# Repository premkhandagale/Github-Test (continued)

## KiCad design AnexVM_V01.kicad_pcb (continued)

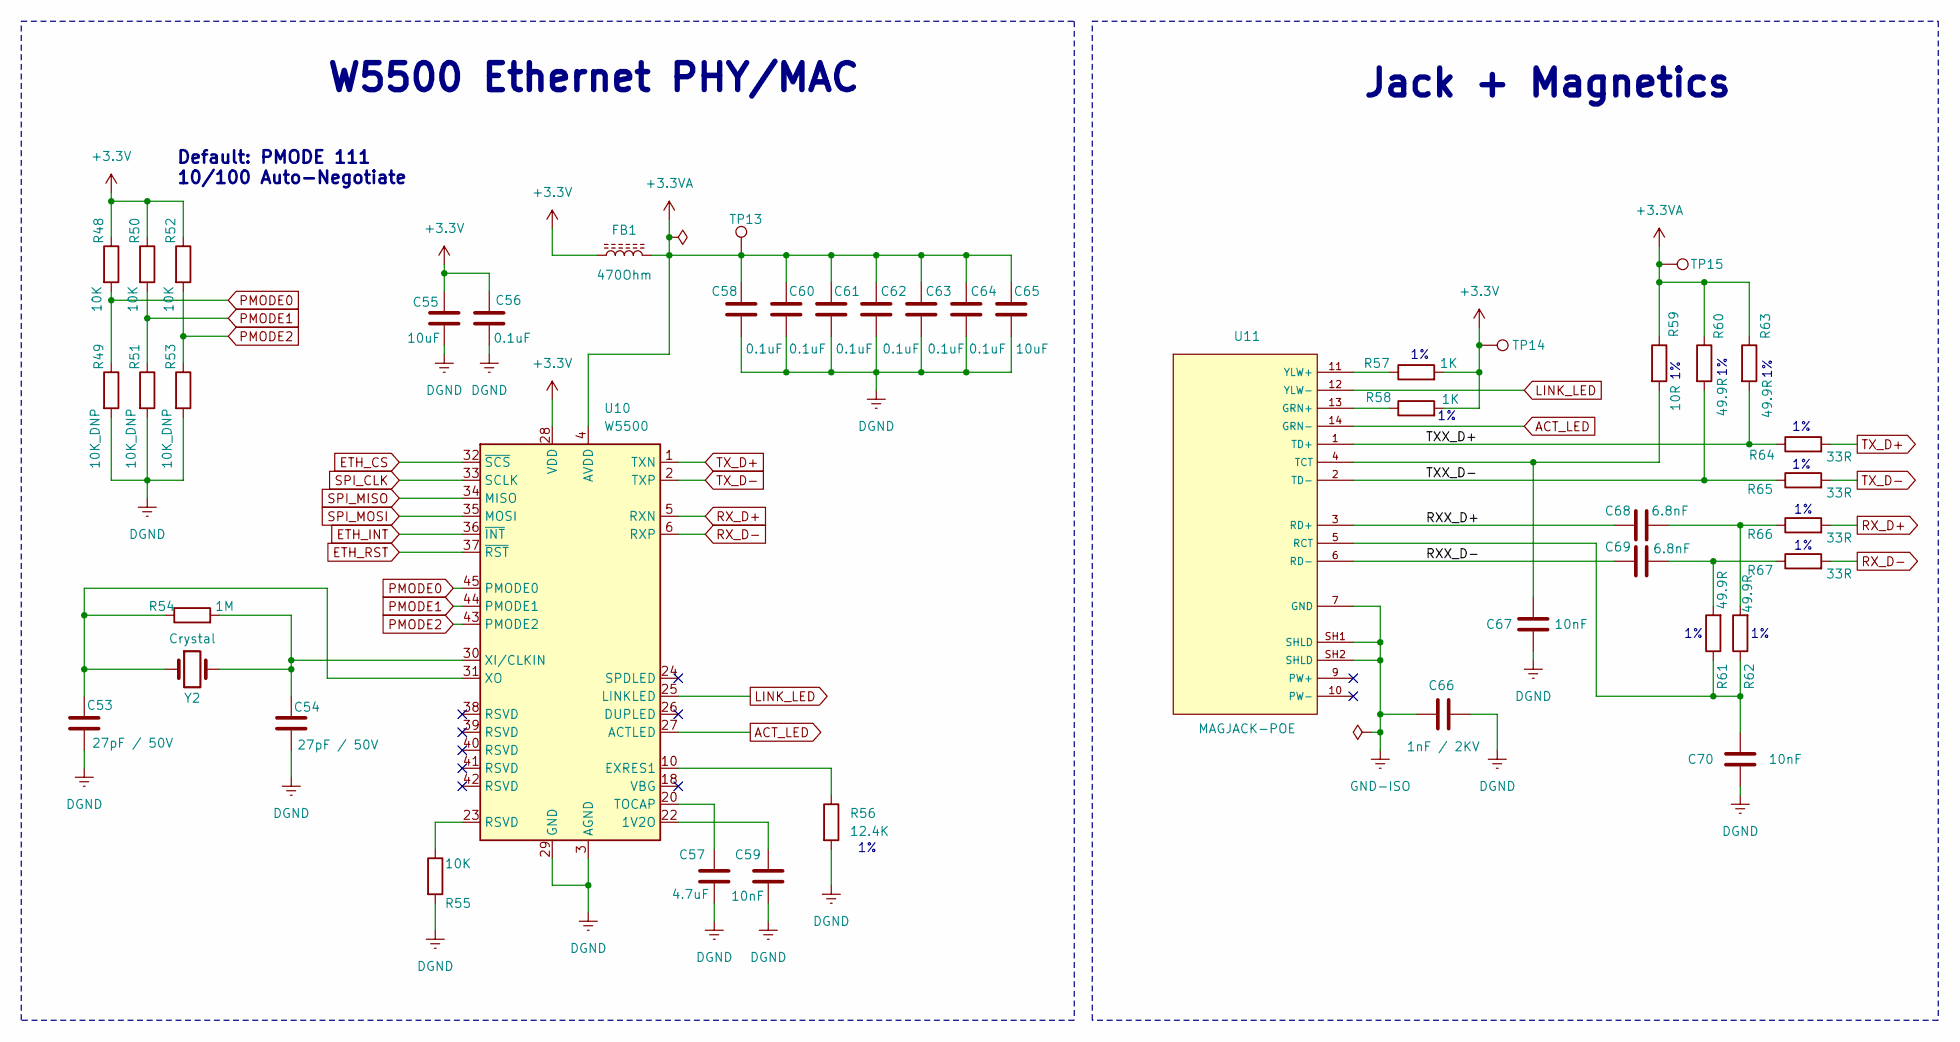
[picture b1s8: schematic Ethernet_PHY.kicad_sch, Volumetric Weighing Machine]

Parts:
C53, C54: 27pF / 50V; C_0603_1608Metric
C55, C65: 10uF; C_0805_2012Metric
C56, C58, C60, C61, C62, C63, C64: 0.1uF; C_0603_1608Metric
C57: 4.7uF; C_0603_1608Metric
C59, C67, C70: 10nF; C_0603_1608Metric
C66: 1nF / 2KV; C_1812_4532Metric
C68, C69: 6.8nF; C_0603_1608Metric
FB1: 470Ohm; D_0603_1608Metric
R48, R50, R52, R55: 10K; R_0603_1608Metric
R49, R51, R53: 10K_DNP; R_0603_1608Metric
R54: 1M; R_0603_1608Metric
R56: 12.4K; R_0603_1608Metric
R57, R58: 1K; R_0603_1608Metric
R59: 10R; R_0603_1608Metric
R60, R61, R62, R63: 49.9R; R_0603_1608Metric
R64, R65, R66, R67: 33R; R_0603_1608Metric
TP13, TP14, TP15: TestPoint; TestPoint_Pad_D1.0mm
U10: W5500; LQFP-48_7x7mm_P0.5mm
U11: MAGJACK-POE; LPJ0284GDNL
Y2: Crystal; XTAL_ECS-250-18-30-JGN-TR

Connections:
+3.3V: C55.1, C56.1, FB1.1, R48.1, R50.1, R52.1, R57.2, R58.2, TP14.1, U10.28 (VDD); also elsewhere on the board
+3.3VA: C58.1, C60.1, C61.1, C62.1, C63.1, C64.1, C65.1, FB1.2, R59.1, R60.1, R63.1, TP13.1, TP15.1, U10.4 (AVDD), U10.8 (AVDD), U10.11 (AVDD), U10.15 (AVDD), U10.17 (AVDD), U10.21 (AVDD)
/Ethernet_PHY/RXX_D+: C68.1, U11.3 (RD+)
/Ethernet_PHY/RXX_D-: C69.1, U11.6 (RD-)
/Ethernet_PHY/TXX_D+: R63.2, R64.1, U11.1 (TD+)
/Ethernet_PHY/TXX_D-: R60.2, R65.1, U11.2 (TD-)
ACT_LED: U10.27 (ACTLED), U11.14 (GRN-)
DGND: C53.2, C54.2, C55.2, C56.2, C57.2, C58.2, C59.2, C60.2, C61.2, C62.2, C63.2, C64.2, C65.2, C66.2, C67.1, C70.1, R49.2, R51.2, R53.2, R55.2, R56.2, U10.3 (AGND), U10.9 (AGND), U10.14 (AGND), U10.16 (AGND), U10.19 (AGND), U10.29 (GND), U10.48 (AGND); also elsewhere on the board
ETH_CS: U10.32 (~SCS); also elsewhere on the board
ETH_INT: U10.36 (~INT); also elsewhere on the board
ETH_RST: U10.37 (~RST); also elsewhere on the board
GND-ISO: C66.1, U11.7 (GND), U11.SH1 (SHLD), U11.SH2 (SHLD)
LINK_LED: U10.25 (LINKLED), U11.12 (YLW-)
unnamed: C68.2, R62.2, R66.1
unnamed: C69.2, R61.2, R67.1
unnamed: R55.1, U10.23 (RSVD)
unnamed: C59.1, U10.22 (1V2O)
unnamed: R56.1, U10.10 (EXRES1)
unnamed: C57.1, U10.20 (TOCAP)
unnamed: C54.1, R54.2, U10.30 (XI/CLKIN), Y2.2
unnamed: C53.1, R54.1, U10.31 (XO), Y2.1
unnamed: R58.1, U11.13 (GRN+)
unnamed: C70.2, R61.1, R62.1, U11.5 (RCT)
unnamed: C67.2, R59.2, U11.4 (TCT)
unnamed: R57.1, U11.11 (YLW+)
PMODE0: R48.2, R49.1, U10.45 (PMODE0)
PMODE1: R50.2, R51.1, U10.44 (PMODE1)
PMODE2: R52.2, R53.1, U10.43 (PMODE2)
RX_D+: R66.2, U10.5 (RXN)
RX_D-: R67.2, U10.6 (RXP)
SPI_CLK: U10.33 (SCLK); also elsewhere on the board
SPI_MISO: U10.34 (MISO); also elsewhere on the board
SPI_MOSI: U10.35 (MOSI); also elsewhere on the board
TX_D+: R64.2, U10.1 (TXN)
TX_D-: R65.2, U10.2 (TXP)

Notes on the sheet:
Jack + Magnetics
Default: PMODE 111 10/100 Auto-Negotiate
W5500 Ethernet PHY/MAC

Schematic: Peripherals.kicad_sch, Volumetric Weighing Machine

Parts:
C36, C40, C41, C42, C43, C44: 1uF; C_0603_1608Metric
C37, C38, C39, C45: 0.1uF; C_0603_1608Metric
J9: DB9-01S; DLS1XS5AK40X
J10, J12, J13: Conn_01x04_Pin; PinHeader_1x04_P2.54mm_Vertical
J11: JHD539; PinHeader_1x12_P2.54mm_Vertical
R41: 10K; R_0603_1608Metric
R42: 560R; R_0603_1608Metric
RV1: 10K_POT; Potentiometer_Bourns_3296W_Vertical
TP12: TestPoint; TestPoint_Pad_D1.0mm
U7: TXS0102DCUR; SOP50P310X90-8N
U8: MAX232; SOIC-16_3.9x9.9mm_P1.27mm

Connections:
+3.3V: C37.2, R41.1, U7.3 (VCCA); also elsewhere on the board
+5V: C38.2, C39.2, C40.2, C44.1, C45.1, J10.1, J11.2 (VDD), J12.1, J13.1, R42.2, RV1.3, TP12.1, U7.7 (VCCB), U8.16 (VCC); also elsewhere on the board
ATMEGA_RX_5V: U7.1 (B2); also elsewhere on the board
ATMEGA_TX_5V: U7.8 (B1); also elsewhere on the board
DGND: C37.1, C38.1, C39.1, C40.1, C41.1, C42.1, C44.2, C45.2, J9.5, J9.MH1, J9.MH2, J10.4, J11.1 (VSS), J11.16 (LED(-)), J12.4, J13.4, RV1.1, U7.2 (GND), U8.15 (GND); also elsewhere on the board
ESP32_RX_3V3: U7.4 (A2); also elsewhere on the board
ESP32_TX_3V3: U7.5 (A1); also elsewhere on the board
LCD_D4: J11.11 (D4); also elsewhere on the board
LCD_D5: J11.12 (D5); also elsewhere on the board
LCD_D6: J11.13 (D6); also elsewhere on the board
LCD_D7: J11.14 (D7); also elsewhere on the board
LCD_EN: J11.6 (E); also elsewhere on the board
LCD_RS: J11.4 (RS); also elsewhere on the board
LCD_RW: J11.5 (R/W); also elsewhere on the board
unnamed: J11.15 (LED(+)), R42.1
unnamed: J11.3 (VO), RV1.2
unnamed: R41.2, U7.6 (OE)
unnamed: C36.2, U8.1 (C1+)
unnamed: C36.1, U8.3 (C1-)
unnamed: C43.2, U8.4 (C2+)
unnamed: C43.1, U8.5 (C2-)
unnamed: J9.3, U8.13 (R1IN)
unnamed: J9.2, U8.14 (T1OUT)
unnamed: C41.2, U8.2 (VS+)
unnamed: C42.2, U8.6 (VS-)
RXD2: U8.12 (R1OUT); also elsewhere on the board
S1_ECHO: J10.3; also elsewhere on the board
S1_TRIG: J10.2; also elsewhere on the board
S2_ECHO: J12.3; also elsewhere on the board
S2_TRIG: J12.2; also elsewhere on the board
S3_ECHO: J13.3; also elsewhere on the board
S3_TRIG: J13.2; also elsewhere on the board
TXD2: U8.11 (T1IN); also elsewhere on the board

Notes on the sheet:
Logic Level Converter - Bi-Directional
16*4 LCD Display
Sensor_3
UART_TO_RS232_INTERFACE
Sensor_1
Sensor_2
Ultrasonic_Module

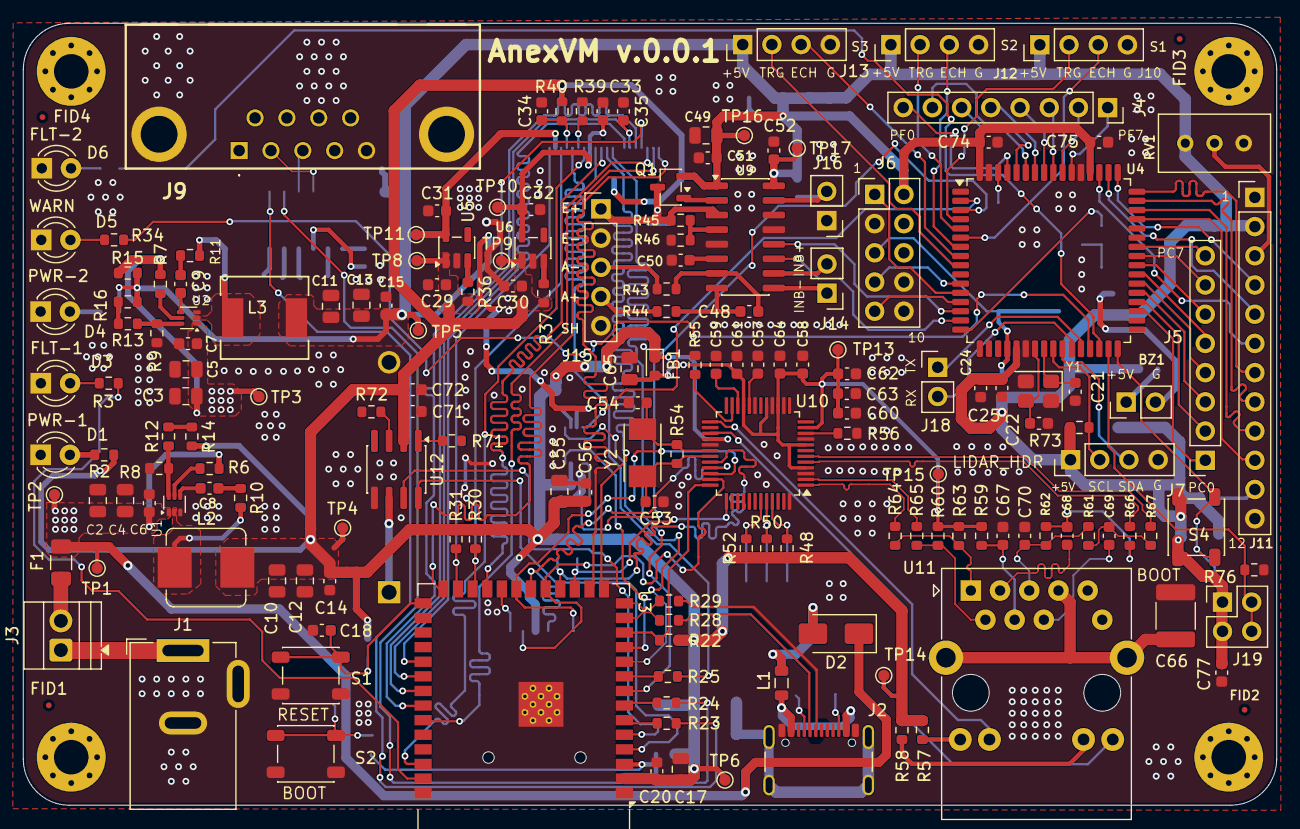
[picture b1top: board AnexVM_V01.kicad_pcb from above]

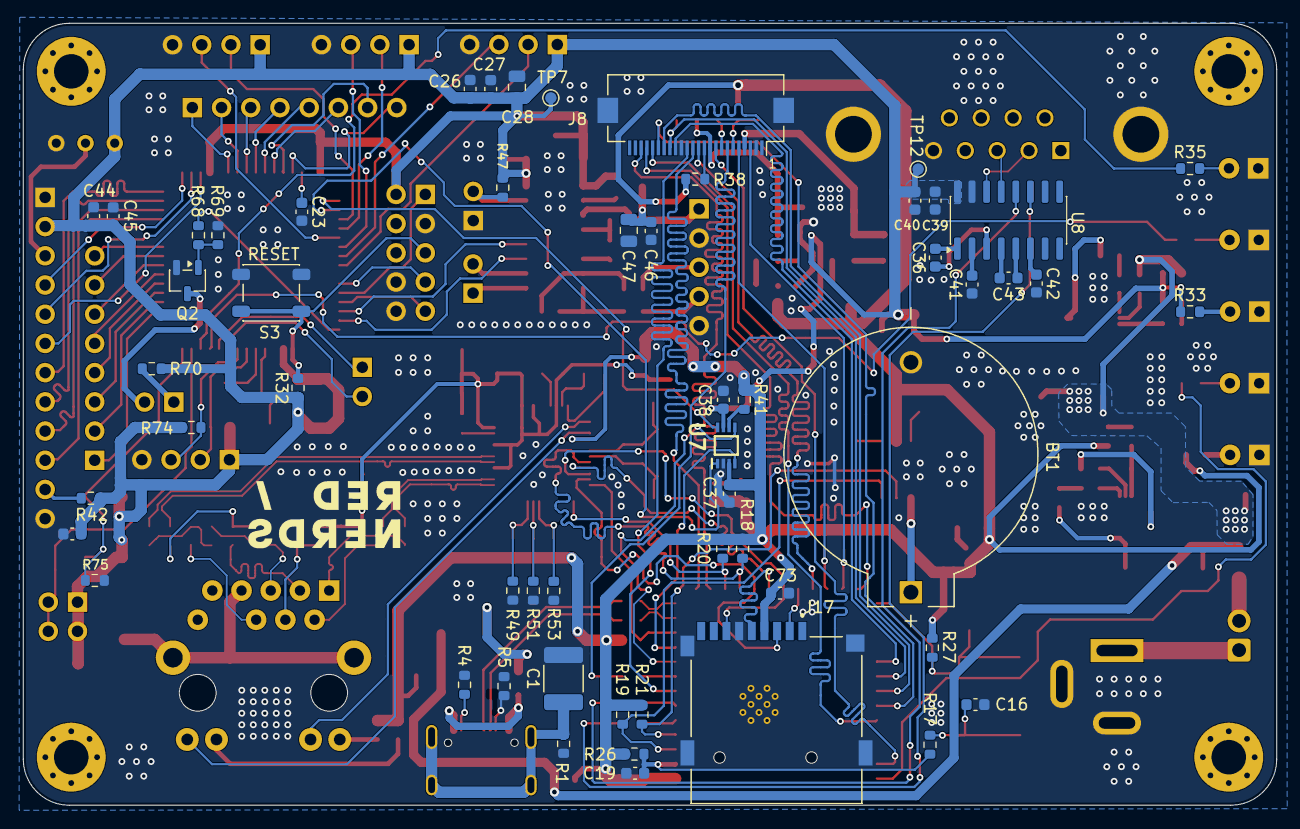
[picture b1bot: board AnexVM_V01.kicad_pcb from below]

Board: 2 copper layers, 109.0 x 68.0 mm, 231 parts (55 on the bottom side), 177 nets.

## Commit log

2026-06-02 Updated Schematic and PCB Layout
